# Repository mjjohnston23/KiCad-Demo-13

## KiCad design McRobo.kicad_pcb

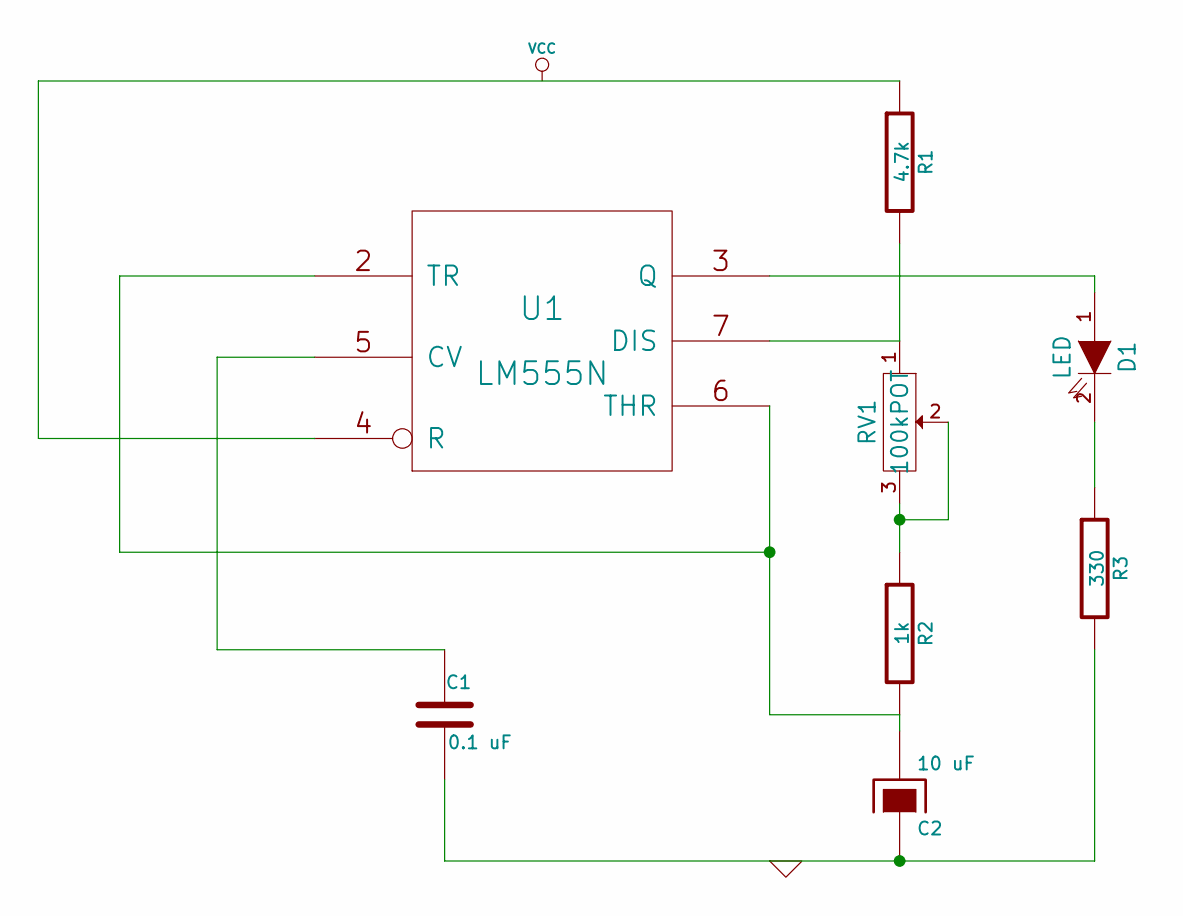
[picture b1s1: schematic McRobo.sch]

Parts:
C1: 0.1 uF
C2: 10 uF
D1: LED
R1: 4.7k
R2: 1k
R3: 330
RV1: 100kPOT
U1: LM555N

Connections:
unnamed: R1.2, RV1.1, U1.7 (DIS)
unnamed: R2.1, RV1.2, RV1.3
unnamed: C1.1, U1.5 (CV)
unnamed: D1.2 (K), R3.1
unnamed: C2.2, R2.2, U1.2 (TR), U1.6 (THR)
unnamed: R1.1, U1.4 (R)
unnamed: D1.1 (A), U1.3 (Q)
unnamed: C1.2, C2.1, R3.2

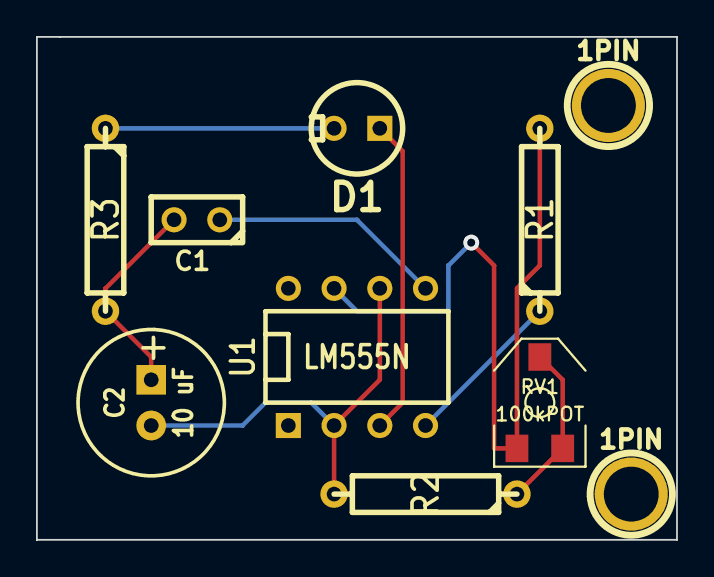
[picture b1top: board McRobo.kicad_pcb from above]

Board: 2 copper layers, 35.6 x 27.9 mm, 10 parts (0 on the bottom side), 8 nets.

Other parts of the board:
1PIN, 1PIN#2: P***; 1pin

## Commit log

2013-10-15 KiCad Files for 15 Oct Meeting
    serenity now serenity now serenity now serenity now serenity now
    serenity now serenity now serenity now serenity now serenity now
    serenity now serenity now serenity now
